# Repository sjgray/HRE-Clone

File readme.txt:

8296 High-Res Emulator (HRE) board clones
=========================================

These are clones of the Commodore 8296 High-Res Emulator (HRE) board. The HRE
is a board plus firmware that emulates the Commodore High-Speed Grahic (HSG)
board which contains a Thomson EF Video Display Processor (VDP). The HRE
firmware implements the same BASIC commands as the HSG but does the drawing
with the 6502 processor rather than the VDP chip.

This is a work-in-progress. It is being cloned using Kicad and some pictures
of the board. The boards are complete but untested. Use at own risk!

PCB........ Kicad Files (work in progress)
   Clone... Original PCB recreation
   Mini.... Compacted version
Firmware... Binary files for Option ROM sockets
Pics....... Renders and (eventually) PCB pics
Software... Demos etc

Steve

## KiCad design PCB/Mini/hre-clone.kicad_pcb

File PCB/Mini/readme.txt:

8296 High-Res Emulator (HRE) board clone
========================================

This is a size-reduced remake of the Commodore 8296 High-Res Emulator
(HRE) board. The HRE is a board plus firmware that emulates the
Commodore High-Speed Grahic (HSG) board which contains a Thomson EF
Video Display Processor (VDP). The HRE firmware implements the same
BASIC commands as the HSG but does the drawing with the 6502 processor
rather than the VDP chip.

This is a work-in-progress. It is being cloned using Kicad and some
pictures of the board. This has not been tested.

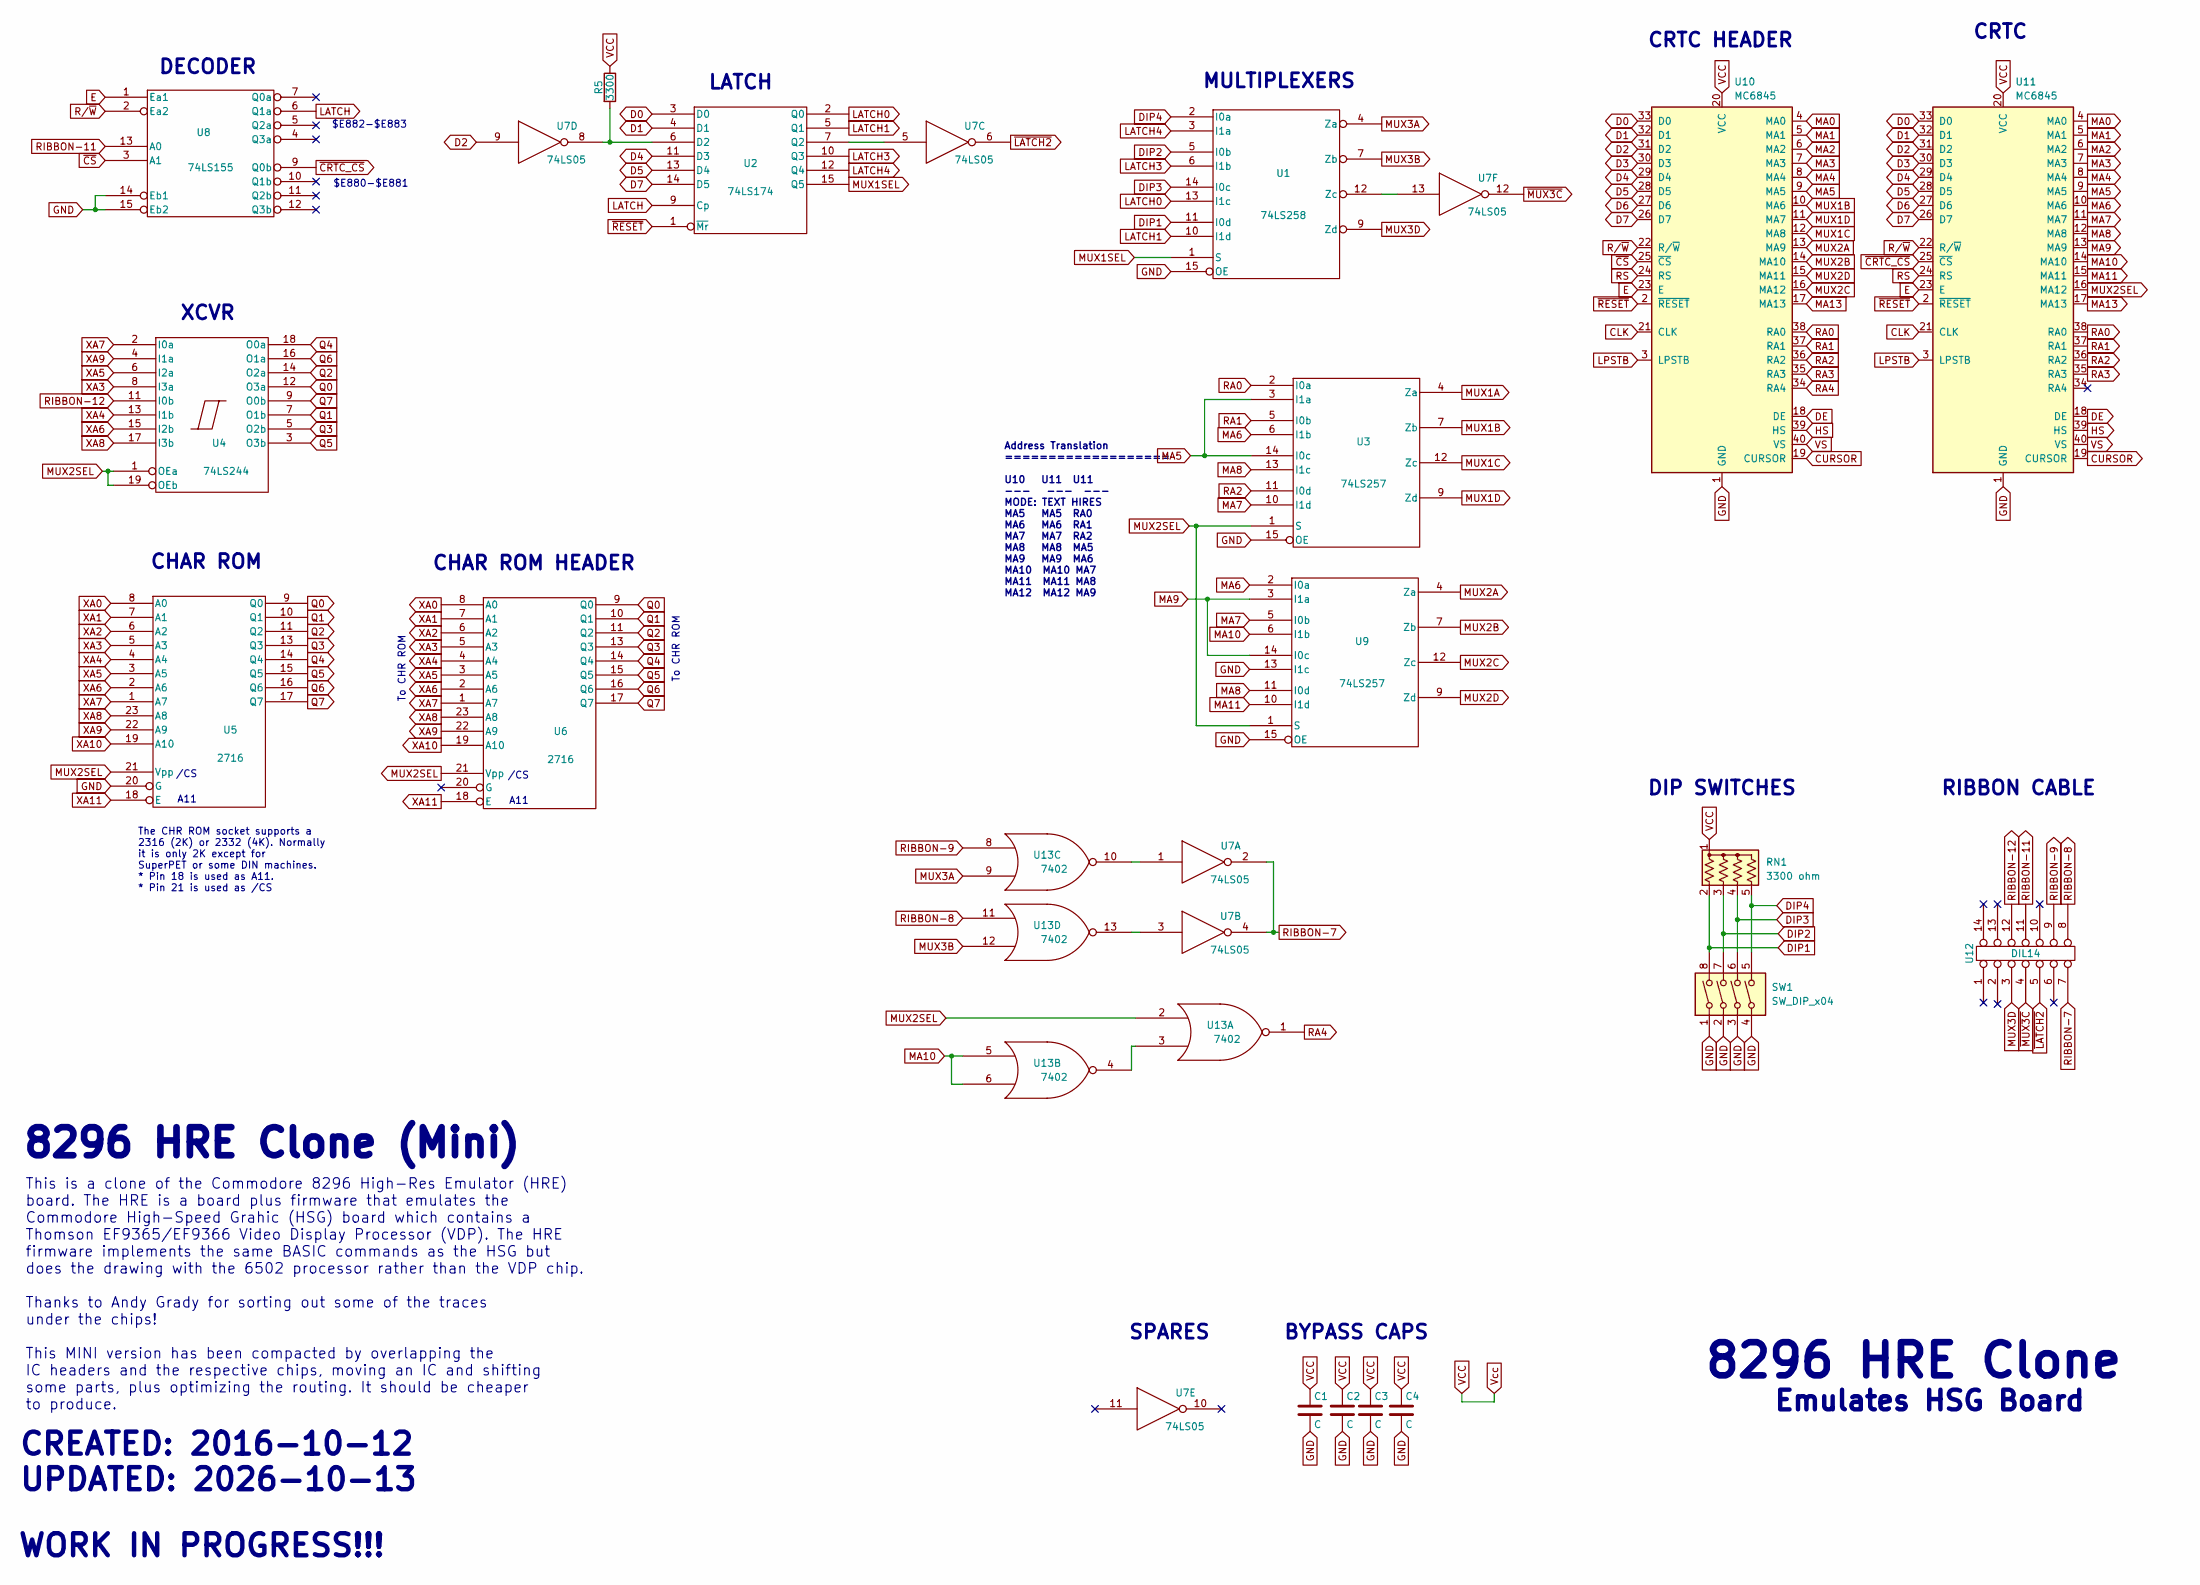
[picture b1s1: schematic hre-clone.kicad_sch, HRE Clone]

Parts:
C1, C2, C3, C4: C; C_Disc_D8.0mm_W2.5mm_P5.00mm
R5: 3300; R_Axial_DIN0309_L9.0mm_D3.2mm_P12.70mm_Horizontal
RN1: 3300 ohm; R_Array_SIP5
SW1: SW_DIP_x04; SW_DIP_SPSTx04_Slide_6.7x11.72mm_W7.62mm_P2.54mm_LowProfile
U1: 74LS258; DIP-16_W7.62mm
U2: 74LS174; DIP-16_W7.62mm
U3, U9: 74LS257; DIP-16_W7.62mm
U4: 74LS244; DIP-20_W7.62mm
U5, U6: 2716; DIP-24_W15.24mm
U7: 74LS05; DIP-14_W7.62mm
U8: 74LS155; DIP-16_W7.62mm
U10, U11: MC6845; DIP-40_W15.24mm
U12: DIL14; DIP-14_W7.62mm
U13: 7402; DIP-14_W7.62mm

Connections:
CLK: U10.21 (CLK), U11.21 (CLK)
CURSOR: U10.19 (CURSOR), U11.19 (CURSOR)
D0: U2.3 (D0), U10.33 (D0), U11.33 (D0)
D1: U2.4 (D1), U10.32 (D1), U11.32 (D1)
D2: U7.9, U10.31 (D2), U11.31 (D2)
D3: U10.30 (D3), U11.30 (D3)
D4: U2.11 (D3), U10.29 (D4), U11.29 (D4)
D5: U2.13 (D4), U10.28 (D5), U11.28 (D5)
D6: U10.27 (D6), U11.27 (D6)
D7: U2.14 (D5), U10.26 (D7), U11.26 (D7)
DE: U10.18 (DE), U11.18 (DE)
DIP1: RN1.2 (R1), SW1.8, U1.11 (I0d)
DIP2: RN1.3 (R2), SW1.7, U1.5 (I0b)
DIP3: RN1.4 (R3), SW1.6, U1.14 (I0c)
DIP4: RN1.5 (R4), SW1.5, U1.2 (I0a)
E: U8.1 (Ea1), U10.23 (E), U11.23 (E)
GND: C1.2, C2.2, C3.2, C4.2, SW1.1, SW1.2, SW1.3, SW1.4, U1.8 (GND), U1.15 (OE), U2.8 (GND), U3.8 (GND), U3.15 (OE), U4.10 (GND), U5.12 (GND), U5.20 (G), U6.12 (GND), U7.7 (GND), U8.8 (GND), U8.14 (Eb1), U8.15 (Eb2), U9.8 (GND), U9.13 (I1c), U9.15 (OE), U10.1 (GND), U11.1 (GND), U13.7 (GND)
HS: U10.39 (HS), U11.39 (HS)
LATCH: U2.9 (Cp), U8.6 (Q1a)
LATCH0: U1.13 (I1c), U2.2 (Q0)
LATCH1: U1.10 (I1d), U2.5 (Q1)
LATCH3: U1.6 (I1b), U2.10 (Q3)
LATCH4: U1.3 (I1a), U2.12 (Q4)
LPSTB: U10.3 (LPSTB), U11.3 (LPSTB)
MA0: U10.4 (MA0), U11.4 (MA0)
MA1: U10.5 (MA1), U11.5 (MA1)
MA2: U10.6 (MA2), U11.6 (MA2)
MA3: U10.7 (MA3), U11.7 (MA3)
MA4: U10.8 (MA4), U11.8 (MA4)
MA5: U3.3 (I1a), U3.14 (I0c), U10.9 (MA5), U11.9 (MA5)
MA6: U3.6 (I1b), U9.2 (I0a), U11.10 (MA6)
MA7: U3.10 (I1d), U9.5 (I0b), U11.11 (MA7)
MA8: U3.13 (I1c), U9.11 (I0d), U11.12 (MA8)
MA9: U9.3 (I1a), U9.14 (I0c), U11.13 (MA9)
MA10: U9.6 (I1b), U11.14 (MA10), U13.5, U13.6
MA11: U9.10 (I1d), U11.15 (MA11)
MA13: U10.17 (MA13), U11.17 (MA13)
MUX1A: U3.4 (Za)
MUX1B: U3.7 (Zb), U10.10 (MA6)
MUX1C: U3.12 (Zc), U10.12 (MA8)
MUX1D: U3.9 (Zd), U10.11 (MA7)
MUX1SEL: U1.1 (S), U2.15 (Q5)
MUX2A: U9.4 (Za), U10.13 (MA9)
MUX2B: U9.7 (Zb), U10.14 (MA10)
MUX2C: U9.12 (Zc), U10.16 (MA12)
MUX2D: U9.9 (Zd), U10.15 (MA11)
MUX2SEL: U3.1 (S), U4.1 (OEa), U4.19 (OEb), U5.21 (Vpp), U6.21 (Vpp), U9.1 (S), U11.16 (MA12), U13.2
MUX3A: U1.4 (Za), U13.9
MUX3B: U1.7 (Zb), U13.12
MUX3D: U1.9 (Zd), U12.3
unnamed: U1.12 (Zc), U7.13
unnamed: R5.2, U2.6 (D2), U7.8
unnamed: U2.7 (Q2), U7.5
unnamed: U13.3, U13.4
unnamed: U7.1, U13.10
unnamed: U7.3, U13.13
Q0: U4.12 (O3a), U5.9 (Q0), U6.9 (Q0)
Q1: U4.7 (O1b), U5.10 (Q1), U6.10 (Q1)
Q2: U4.14 (O2a), U5.11 (Q2), U6.11 (Q2)
Q3: U4.5 (O2b), U5.13 (Q3), U6.13 (Q3)
Q4: U4.18 (O0a), U5.14 (Q4), U6.14 (Q4)
Q5: U4.3 (O3b), U5.15 (Q5), U6.15 (Q5)
Q6: U4.16 (O1a), U5.16 (Q6), U6.16 (Q6)
Q7: U4.9 (O0b), U5.17 (Q7), U6.17 (Q7)
RA0: U3.2 (I0a), U10.38 (RA0), U11.38 (RA0)
RA1: U3.5 (I0b), U10.37 (RA1), U11.37 (RA1)
RA2: U3.11 (I0d), U10.36 (RA2), U11.36 (RA2)
RA3: U10.35 (RA3), U11.35 (RA3)
RA4: U10.34 (RA4), U13.1
RIBBON-7: U7.2, U7.4, U12.7
RIBBON-8: U12.8, U13.11
RIBBON-9: U12.9, U13.8
RIBBON-11: U8.13 (A0), U12.11
RIBBON-12: U4.11 (I0b), U12.12
RS: U10.24 (RS), U11.24 (RS)
R/~W: U8.2 (Ea2), U10.22 (R/~W), U11.22 (R/~W)
VCC: C1.1, C2.1, C3.1, C4.1, R5.1, RN1.1 (common), U1.16 (VCC), U2.16 (VCC), U3.16 (VCC), U4.20 (VCC), U5.24 (Vcc), U6.24 (Vcc), U7.14 (VCC), U8.16 (VCC), U9.16 (VCC), U10.20 (VCC), U11.20 (VCC), U13.14 (VCC)
VS: U10.40 (VS), U11.40 (VS)
XA0: U5.8 (A0), U6.8 (A0)
XA1: U5.7 (A1), U6.7 (A1)
XA2: U5.6 (A2), U6.6 (A2)
XA3: U4.8 (I3a), U5.5 (A3), U6.5 (A3)
XA4: U4.13 (I1b), U5.4 (A4), U6.4 (A4)
XA5: U4.6 (I2a), U5.3 (A5), U6.3 (A5)
XA6: U4.15 (I2b), U5.2 (A6), U6.2 (A6)
XA7: U4.2 (I0a), U5.1 (A7), U6.1 (A7)
XA8: U4.17 (I3b), U5.23 (A8), U6.23 (A8)
XA9: U4.4 (I1a), U5.22 (A9), U6.22 (A9)
XA10: U5.19 (A10), U6.19 (A10)
XA11: U5.18 (E), U6.18 (E)
~CRTC_CS: U8.9 (Q0b), U11.25 (~CS)
~CS: U8.3 (A1), U10.25 (~CS)
~LATCH2: U7.6, U12.5
~MUX3C: U7.12, U12.4
~RESET: U2.1 (~Mr), U10.2 (~RESET), U11.2 (~RESET)

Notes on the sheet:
LATCH
CHAR ROM
WORK IN PROGRESS!!!
This is a clone of the Commodore 8296 High-Res Emulator (HRE) board. The HRE is a board plus firmware that emulates the Commodore High-Speed Grahic (HSG) board which contains a Thomson EF9365/EF9366 Video Display Processor (VDP). The HRE firmware implements the same BASIC commands as the HSG but do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
8296 HRE Clone (Mini)
XCVR
DIP SWITCHES
To CHR ROM
$E880-$E881
CRTC HEADER
Emulates HSG Board
Address Translation =================== U10 U11 U11 --- --- --- MODE: TEXT HIRES MA5 MA5 RA0 MA6 MA6 RA1 MA7 MA7 RA2 MA8 MA8 MA5 MA9 MA9 MA6 MA10 MA10 MA7 MA11 MA11 MA8 MA12 MA12 MA9
MULTIPLEXERS
CRTC
CHAR ROM HEADER
SPARES
A11
The CHR ROM socket supports a 2316 (2K) or 2332 (4K). Normally it is only 2K except for SuperPET or some DIN machines. * Pin 18 is used as A11. * Pin 21 is used as /CS
/CS
8296 HRE Clone
BYPASS CAPS
RIBBON CABLE
CREATED: 2016-10-12 UPDATED: 2026-10-13
$E882-$E883
DECODER

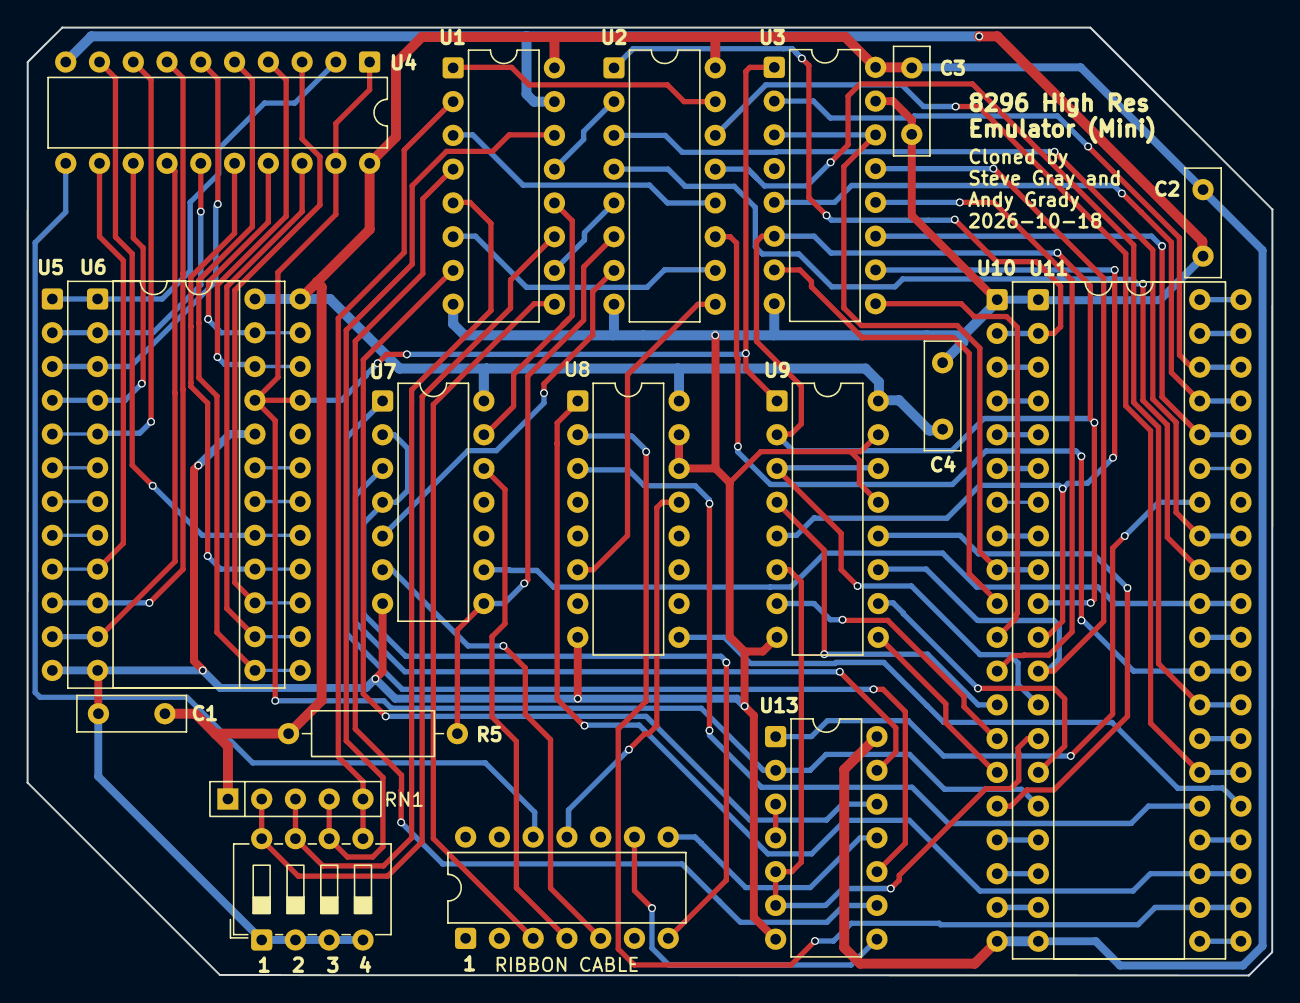
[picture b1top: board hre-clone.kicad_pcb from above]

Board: 2 copper layers, 93.6 x 71.3 mm, 20 parts (0 on the bottom side), 94 nets.
